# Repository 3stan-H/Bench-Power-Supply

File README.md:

# Bench Power Supply

## Overview
A mains-powered, adjustable bench power supply designed in KiCad, converting 120V AC wall input into a regulated 1–20V DC output. The design integrates real-time voltage/current monitoring and follows mains electrical safety practices for isolating AC and low-voltage DC domains. The complete unit was built for approximately $90 in components — roughly 50% less than similarly-specced commercial digital bench supplies ($130–$200 retail).

## Objectives
- Design a safe, mains-powered adjustable DC power supply from raw 120V AC input
- Provide fine-grained, real-time output voltage adjustment
- Display live output voltage and current readings during use
- Follow mains electrical safety practices to protect against shock hazards
- Deliver the unit at a significant cost saving over comparable commercial supplies

## Key Components
- **AC Input Stage** — IEC inlet, fuse, step-down transformer, bridge rectifier
- **Buck Converter** — XL4016, regulating output to 2–5V DC
- **Feedback Network** — potentiometer + resistor divider on the buck converter's feedback pin, enabling 0.01V adjustment resolution
- **Current Sensing** — INA219 current-sensing IC
- **Display/Control** — Arduino Nano driving an LCD screen, showing live voltage/current accurate to 0.01V/0.01A

## Signal Chain
IEC Inlet → Fuse → Transformer → Bridge Rectifier → XL4016 Buck Converter → Regulated 2–5V DC Output

## Files
- `Bench_Power_Supply.kicad_pro` — project file
- `Bench_Power_Supply.kicad_sch` — full schematic (AC input stage, buck converter, feedback network, current-sensing and display circuitry)
- `Bench_Power_Supply.kicad_pcb` — PCB layout (AC-safety and low-voltage DC routing kept separate)
- `gerbers/` — fabrication output (Gerber, drill files)
- `firmware/` — Arduino Nano source code for the INA219 readout and LCD display
- `Bench_Power_Supply_3D.png` — 3D rendered board preview

## Design Notes
- **Voltage Regulation**: The XL4016 buck converter's feedback pin is tuned via a potentiometer/resistor-divider network, giving real-time output adjustment in 0.01V steps across the 1–20V range.
- **Monitoring**: An INA219 current-sensing IC feeds live voltage and current data to an Arduino Nano, which drives an LCD display accurate to 0.01V/0.01A for real-time monitoring during use.
- **Mains Safety**: The chassis (earth) ground is isolated from the circuit's PCB ground rail at the IEC inlet, protecting against electrical shock hazards. AC-safety and low-voltage DC routing are kept physically separated on the PCB layout.
- **Cost**: Total build cost was approximately $90 in components, roughly 50% less than similarly-specced commercial digital bench power supplies (typically $130–$200 retail).

## Status
Designed, laid out, and built as a complete working unit — power regulation, voltage adjustment, and live voltage/current monitoring were all implemented and verified in the final build.

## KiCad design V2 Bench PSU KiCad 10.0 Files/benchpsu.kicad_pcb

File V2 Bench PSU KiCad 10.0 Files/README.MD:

This folder contains the same project however the errors that came up when assemblying the first version was fixed. This includes the missing ground on J4, as well as fixing the Pins of D1. Also includes the full BOM with the new schematic representing all the symbols. The BOM represents the materials and components needed for this project with the MPN refering to the digikey part number. 

The BOM Also is missing a couple of things which include:

- Jumper Wires (MPN: 1954)
- 2x Potentiometers (MPN: PDB181-E420K-103B)

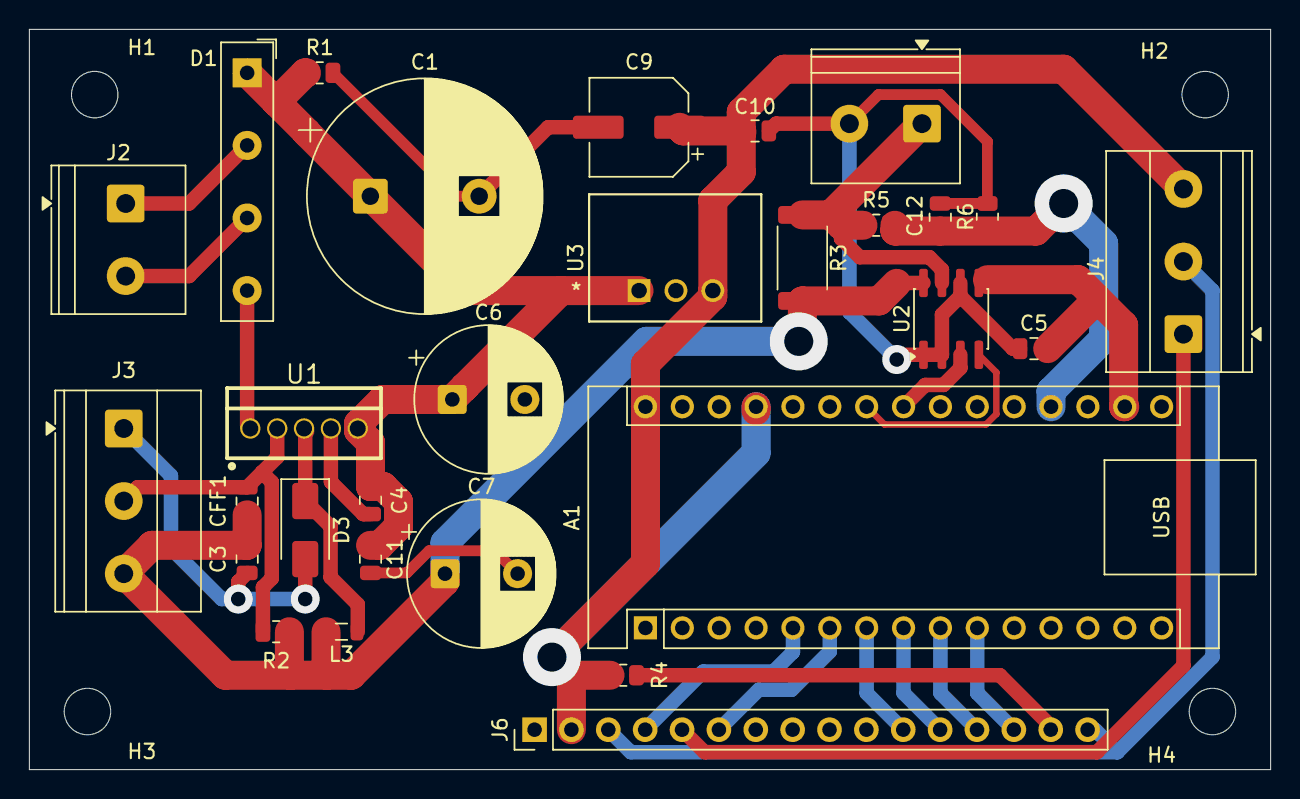
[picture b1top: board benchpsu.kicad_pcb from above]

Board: 2 copper layers, 85.5 x 51.0 mm, 33 parts (0 on the bottom side), 22 nets.

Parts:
A1: Arduino_Nano_v3.x; Arduino_Nano
C1: 4700u/50V; CP_Radial_D16.0mm_P7.50mm
C3, C4, C11: 1u; C_0805_2012Metric
C5, C10, C12: 100n; C_0805_2012Metric
C6: 470u/50V; CP_Radial_D10.0mm_P5.00mm
C7: 1000u/25V; CP_Radial_D10.0mm_P5.00mm
C9: 100u/16V; CP_Elec_6.3x5.4
CFF1: 33n; C_0805_2012Metric
D1: GBU1010; Diode_Bridge_19.0x3.5x10.0mm_P5.0mm
D3: SS34; D_SMA
H1, H2, H3, H4: MountingHole; MountingHole_3.2mm_M3
J2, J5: Screw_Terminal_01x02; TerminalBlock_Phoenix_PT-1,5-2-5.0-H_1x02_P5.00mm_Horizontal
J3, J4: Screw_Terminal_01x03; TerminalBlock_Phoenix_MKDS-1,5-3_1x03_P5.00mm_Horizontal
J6: Connects to LCD; PinHeader_1x16_P2.54mm_Vertical
L3: 100u; L_0805_2012Metric
R1, R6: 10k; R_0805_2012Metric
R2: 3.3k; R_0805_2012Metric
R3: 0.1; R_2512_6332Metric
R4: 100; R_0805_2012Metric
R5: 47k; R_0805_2012Metric
U1: XL4016
U2: INA219AxD; SOIC-8_3.9x4.9mm_P1.27mm
U3: R-78C5.0-1.0; R-78C&slash_E-1.0_SIP3_11.6X8.5X10.4_RCP

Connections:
/3.3V: A1.17 (3V3), C5.1, U2.5 (VS)
/5V: A1.27 (+5V), A1.30 (VIN), C9.1, C10.1, J4.3, J6.2, R4.2, U3.3 (VO)
/+VOUT: C3.1, C7.1, CFF1.2, J3.3, L3.2, R2.1, R3.1, U2.8 (IN+)
/+VOUT_SENSE: J5.1, R3.2, R5.2, U2.7 (IN-)
/+VRAW: C1.1, C4.1, C6.1, C11.1, D1.1 (+), R1.1, U1.5 (VIN), U3.1 (VI)
/D2: A1.5 (D2), J6.4
/D3: A1.6 (D3), J6.6
/D4: A1.7 (D4), J6.11
/D5: A1.8 (D5), J6.12
/D6: A1.9 (D6), J6.13
/D7: A1.10 (D7), J6.14
/DS1PIN15: J6.15, R4.1
/J4PIN1: J4.1, J6.5
/SCL: A1.24 (A5), U2.4 (SCL)
/SDA: A1.23 (A4), U2.3 (SDA)
/ScrewTerminal1: D1.2, J2.1
/ScrewTerminal2: D1.3 (-), J2.2
/VOUT_SENSE: A1.19 (A0), C12.1, R5.1, R6.1
GND: A1.4 (GND), A1.29 (GND), C1.2, C3.2, C5.2, C6.2, C7.2, C9.2, C10.2, C11.2, C12.2, D1.4, D3.2 (A), J3.1, J4.2, J5.2, J6.1, J6.3, J6.16, R1.2, R6.2, U1.1 (GND), U2.1 (A1), U2.2 (A0), U2.6 (GND), U3.2 (GND)
unnamed: D3.1 (K), L3.1, U1.3 (OUT)
unnamed: CFF1.1, J3.2, R2.2, U1.2 (FB)
unnamed: C4.2, U1.4 (VC)

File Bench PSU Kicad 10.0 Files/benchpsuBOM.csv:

"Reference","Qty","Value","Footprint","LCSC","MPN"
"A1","1","Arduino_Nano_v3.x","Module:Arduino_Nano","","102010019"
"C1","1","4700u/50V","Capacitor_THT:CP_Radial_D16.0mm_P7.50mm","C5115284",""
"C3,C4,C11","3","1u","Capacitor_SMD:C_0805_2012Metric","C28323",""
"C5,C10,C12","3","100n","Capacitor_SMD:C_0805_2012Metric","C126469 ",""
"C6","1","470u/50V","Capacitor_THT:CP_Radial_D10.0mm_P5.00mm","C346975",""
"C7","1","1000u/25V","Capacitor_THT:CP_Radial_D10.0mm_P5.00mm","C503217",""
"C9","1","100u/16V","Capacitor_SMD:CP_Elec_6.3x5.4","C346929",""
"CFF1","1","33n","Capacitor_SMD:C_0805_2012Metric","C1739",""
"D1","1","GBU1010","Diode_THT:Diode_Bridge_19.0x3.5x10.0mm_P5.0mm","","GBU1010"
"D3","1","SS34","Diode_SMD:D_SMA","C8678",""
"DS1","1","WC1602A","","","181"
"F1","1","Fuse","","","5HT 2-R"
"J1","1","IEC_60320_C14_Receptacle","","","723W-X2/03"
"J2,J5","2","Screw_Terminal_01x02","TerminalBlock_Phoenix:TerminalBlock_Phoenix_PT-1,5-2-5.0-H_1x02_P5.00mm_Horizontal","","282837-2"
"J3,J4","2","Screw_Terminal_01x03","TerminalBlock_Phoenix:TerminalBlock_Phoenix_MKDS-1,5-3_1x03_P5.00mm_Horizontal","","282837-3"
"J6","1","Connects to LCD","Connector_PinHeader_2.54mm:PinHeader_1x16_P2.54mm_Vertical","C7430372",""
"L3","1","100u","Inductor_SMD:L_0805_2012Metric","C88184",""
"R1,R6","2","10k","Resistor_SMD:R_0805_2012Metric","C17414",""
"R2","1","3.3k","Resistor_SMD:R_0805_2012Metric","C26010",""
"R3","1","0.1","Resistor_SMD:R_2512_6332Metric","C844904",""
"R4","1","100","Resistor_SMD:R_0805_2012Metric","C702827",""
"R5","1","47k","Resistor_SMD:R_0805_2012Metric","C29252",""
"T1","1","Transformer_1P_1S","","","VPS24-3300"
"U1","1","XL4016","Package_TO_SOT_SMD:XL4016","C55881",""
"U2","1","INA219AxD","Package_SO:SOIC-8_3.9x4.9mm_P1.27mm","C138706",""
"U3","1","R-78C5.0-1.0","Converter_DCDC:R-78C&slash_E-1.0_SIP3_11.6X8.5X10.4_RCP","","R-78C5.0-1.0"
